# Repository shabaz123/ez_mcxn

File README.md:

# EZ-MCXN

This repository contains NXP MCXN related content.

# MCXN236 Test Board

This test board is intended for trying out the MCXN236VKLT microcontroller (100-pin HLQFP 0.5 mm package). The 235 variant is also possible, and there's a good chance the MCXN547VKLT microcontroller will work too.

# MCX Projects

This folder contains a board config and example blinky application source code. The folders may be hard-coded in places; the mcx\_projects folder can be placed at `c:\dev\projects` to keep things seamless, otherwise you may need to edit files.

# Environment Variables

The following user vars (environment variables) will need to be created:

`ARMGCC_DIR = C:\DEV\arm_gnu_toolchains\15.2.rel1 `(this folder should contain bin, include, lib folders and so on)

`MCUXPRESSO_SDK_ROOT = C:\dev\projects\mcuxpresso-sdk\mcuxsdk`

# Double Blinky

## Overview

Double Blinky is a simple MCUXpresso SDK project that blinks two LEDs.

The example uses:

* LED1: P3_6
* LED2: P3_1

Both LEDs are active high.

The project also provides a simple starting point for creating new projects using the EZ-MCXN board configuration.

## Prerequisites

The following are required:

* MCUXpresso SDK installed under `C:\dev\projects\mcuxpresso-sdk`
* Arm GNU Toolchain
* CMake and Ninja
* Python
* MCUXpresso Config Tools
* NXP Secure Provisioning SDK (SPSDK), installed by typing: `py -m pip install spsdk`
* `west`

The project workspace is expected to be:

```text
C:\dev\projects\mcx_projects
```

For example:

```text
C:\dev\projects\mcx_projects\
├── _boards\
│   └── ez_mcxn\
└── double_blinky\
```

The `MCUXPRESSO_SDK_ROOT` environment variable must point to the MCUXpresso SDK:

```text
C:\dev\projects\mcuxpresso-sdk\mcuxsdk
```

## Building the Project

Open PowerShell in the project directory:

```powershell
cd C:\dev\projects\mcx_projects\double_blinky
```

One-time, you may need to enable permissions by typing:
```
Unblock-File .\build.ps1
```

For a clean build:

```powershell
.\build.ps1 clean
.\build.ps1 build debug
```

The build output is placed in:

```text
double_blinky\output
```

The main generated files are:

```text
output\double_blinky.elf
output\double_blinky.bin
```

Useful build commands are:

```powershell
.\build.ps1
.\build.ps1 clean
.\build.ps1 debug
.\build.ps1 release
.\build.ps1 menuconfig
.\build.ps1 list
.\build.ps1 flash
```

The commands have the following purposes:

* `.\build.ps1` - Builds the project using the debug build configuration.
* `.\build.ps1 clean` - Cleans compiled files from the existing build. Use this after changing board files, Kconfig settings or CMake files, or if a normal build behaves unexpectedly. Also, do this whenever changing between debug and release builds.
* `.\build.ps1 release` - Builds the project using the debug build configuration.
* `.\build.ps1 menuconfig` - Opens the interactive Kconfig configuration interface, allowing SDK and project configuration options to be viewed or changed.
* `.\build.ps1 list` - Displays the project/build configuration being used by the script, such as the board, SDK, toolchain and build directory.
* * `.\build.ps1 flash` - Uses SPSDK to flash the microcontroller. Before executing this command, hold down the BOOT button and reset the microcontroller, then release the BOOT button.

For normal source-code changes, for debug builds, `.\build.ps1` is usually sufficient. Use `clean` after changing the board configuration, Kconfig files or CMake files.

## Creating a New Project

`double_blinky` can be used as a template for another application.

Copy the project folder and give it a new name. For example:

```text
C:\dev\projects\mcx_projects\testproj
```

Then:

1. In `CMakeLists.txt`, change the project name from `double_blinky` to `testproj`.
2. In `Kconfig`, change the displayed project name.
3. Modify `main.c` for the new application.
4. For VS Code IntelliSense Syntax Highlighting to work well, edit the file `mcx_projects\.vscode\c_cpp_properties.json` to add your project folder in the `compileCommands` section. Note: For IntelliSense to fully work, open the top folder `mcx_projects`, not the individual project folder. You may need to restart VS Code after performing a first build for each project, for IntelliSense to fully work, because it relies on a file that gets generated and placed in the project folder output subdirectory.
5. Build with:

```powershell
.\build.ps1 debug
```

The existing `ez_mcxn` board configuration can be shared by multiple projects.

## Board Configuration

Board configurations are stored in:

```text
C:\dev\projects\mcx_projects\_boards
```

The board used by this project is:

```text
C:\dev\projects\mcx_projects\_boards\ez_mcxn
```

The important files include:

```text
ez_mcxn\
├── board\
├── board.c
├── board.h
├── CMakeLists.txt
├── EZ_MXCN.mex
├── Kconfig
├── Kconfig.defconfig
├── prj.conf
└── variable.cmake
```

The `board` subfolder contains files generated by MCUXpresso Config Tools, such as:

```text
clock_config.c
clock_config.h
peripherals.c
peripherals.h
pin_mux.c
pin_mux.h
```

Do not normally edit these generated files manually.

## Adding or Modifying Peripherals

Launch MCUXpresso Config Tools and open:

```text
C:\dev\projects\mcx_projects\_boards\ez_mcxn\EZ_MXCN.mex
```

Use Config Tools to modify pins, clocks and peripherals.

When finished, use **Update Code** to regenerate the files in the `board` subfolder.

Then rebuild the application:

```powershell
.\build.ps1 clean
.\build.ps1 debug
```

## Creating a New Board Configuration

If a project needs different hardware without changing the shared `ez_mcxn` configuration, make a copy of the board folder.

For example:

```text
C:\dev\projects\mcx_projects\_boards\myboard
```

Update the board name where required, particularly in:

```text
Kconfig
variable.cmake
board.h
```

Rename the `.mex` file if desired, open it with MCUXpresso Config Tools, make the required pin, clock and peripheral changes, and run **Update Code**.

Finally, change the `$Board` setting in the project's `build.ps1`:

```powershell
$Board = "myboard"
```

Then perform a clean build.

## EZ-MCXN Hardware

The current EZ-MCXN configuration uses:

* MCU: MCXN236
* Main crystal: 24 MHz
* RTC crystal: 32.768 kHz
* System clock: 150 MHz
* LED1: P3_6, active high
* LED2: P3_1, active high
* UART RX: P1_8
* UART TX: P1_9
* UART: LP_FLEXCOMM4 / LPUART
* UART baud rate: 115200

## Debugging and Programming

### Using a Debug Probe

A compatible SWD debug probe, for example MCU-Link, can be used for programming and debugging.

Build the project first using:

```powershell
.\build.ps1 debug
```

The ELF file for debugging/programming is then available at:

```text
output\double_blinky.elf
```

### Programming Without a Debug Probe

The MCXN236 contains a ROM-based ISP (In-System Programming) bootloader. This makes it possible to program the internal flash without an SWD debug probe.

The ROM bootloader supports several communication interfaces, including USB HID.

The EZ-MCXN board has a USB connector connected to the MCU USB signals and push-buttons labelled `BOOT LOAD` and `RESET`.

To enter ROM ISP mode:

1. Connect the EZ-MCXN USB connector to the PC.
2. Press and hold `BOOT LOAD`.
3. While continuing to hold `BOOT LOAD`, press and release `RESET`.
4. Release `BOOT LOAD`.

The MCXN236 should now be running its built-in ROM ISP bootloader rather than the application in flash.

If you installed NXP SPSDK (mentioned earlier) then afer you've pressed the buttons to get into the bootloader mode, type:
```
.\build.ps1 flash
```

If all goes well, the new firmware will start running!

The PC can communicate with the ROM bootloader using NXP's `blhost` command-line utility or MCUXpresso Secure Provisioning Tool (the above command uses the Python SPSDK install, view the contents of the `build.ps1` file to see the commands that were used).

A useful first test with `blhost` is to ask the bootloader for its version/property information. For USB HID, `blhost` uses the USB VID/PID of the ROM bootloader.

For example, the MCXN236 ROM ISP used on NXP's FRDM-MCXN236 is accessible with:

```powershell
blhost -u 0x1FC9,0x0158 -- get-property 1
```

If this succeeds, the PC is communicating with the MCXN236 ROM bootloader.

The application binary produced by this project is:

```text
output\double_blinky.bin
```

For an unsecured development device using the normal internal-flash boot configuration, firmware can be written to the beginning of internal flash using the ROM ISP tools.

NXP's MCUXpresso Secure Provisioning Tool is recommended when initially setting up or verifying this process because it provides a GUI for selecting the MCXN236, establishing the ISP connection, preparing the image and programming the device.

After programming is complete, press `RESET` without holding `BOOT LOAD`. The MCU should then boot the application normally from internal flash.

> **Note:** ROM ISP is different from installing a custom USB DFU bootloader. The MCXN236 ROM bootloader is already built into the chip and cannot be accidentally erased with the application. Secure-boot, lifecycle and CMPA configuration can change what the ROM permits, so the simple procedure above assumes an unsecured development device with the normal internal-flash boot configuration.

# EZ_MCXN Pin Allocations
<!-- info: table: widths="6% 16% 6% 18% 6% 21% 6% 21%" -->

| Pin | Use           | Pin | Use               | Pin | Use       | Pin | Use                         |
| :-- | :------------ | :-- | :---------------- | :-- | :-------- | :-- | :-------------------------- |
| 1   | UART\_RXD     | 26  | HDR\_PORT4        | 51  | SPARE(TP) | 76  | SWDIO                       |
| 2   | UART\_TXD     | 27  | HDR\_PORT4        | 52  | 0V        | 77  | SWCLK                       |
| 3   | CANTX         | 28  | HDR\_PORT4        | 53  | N/C       | 78  | SWO                         |
| 4   | CANRX         | 29  | HDR\_PORT4        | 54  | 3.3V      | 79  | SPARE(TP)                   |
| 5   | HDR\_PORT1    | 30  | 3.3V via FBEAD    | 55  | Cap to 0V | 80  | PDM\_CLM                    |
| 6   | HDR\_PORT1    | 31  | 3.3V via FBEAD    | 56  | TFT\_DC   | 81  | PDM\_DAT                    |
| 7   | HDR\_PORT1    | 32  | 0V                | 57  | TFT\_RST  | 82  | BOOT\_BTN\_CAP\_AND\_PULLUP |
| 8   | HDR\_PORT1    | 33  | 0V                | 58  | Cap to 0V | 83  | 3.3V                        |
| 9   | RST (R/C/BTN) | 34  | 3.3V              | 59  | 3.3V      | 84  | I2C\_SDA                    |
| 10  | XTAL          | 35  | HDR\_PORT4GENERAL | 60  | TFT\_CS   | 85  | I2C\_SCL                    |
| 11  | EXTAL         | 36  | HDR\_PORT4GENERAL | 61  | TFT\_BL   | 86  | PDM\_DAT1                   |
| 12  | Short to 58   | 37  | HDR\_PORT4GENERAL | 62  | KEY\_ROW1 | 87  | SPARE(TP)                   |
| 13  | 3.3V          | 38  | HDR\_PORT4GENERAL | 63  | KEY\_ROW2 | 88  | microSD MOSI                |
| 14  | I2S\_A\_BCLK  | 39  | HDR\_PORT4GENERAL | 64  | KEY\_ROW3 | 89  | microSD SCK                 |
| 15  | I2S\_A\_LRCLK | 40  | USBDP             | 65  | KEY\_ROW4 | 90  | microSD MISO                |
| 16  | I2S\_B\_DAT   | 41  | USBDM             | 66  | 3.3V      | 91  | microSD CS                  |
| 17  | I2S\_A\_DAT   | 42  | USB\_VBUS         | 67  | KEY\_COL1 | 92  | TFT\_MOSI                   |
| 18  | I2S\_A\_DAT1  | 43  | 0V                | 68  | KEY\_COL2 | 93  | TFT\_SCK                    |
| 19  | I2S\_B\_DAT1  | 44  | 3.3V              | 69  | KEY\_COL3 | 94  | TFT\_MISO                   |
| 20  | I2S\_B\_BCLK  | 45  | NC/DP             | 70  | KEY\_COL4 | 95  | HDR\_PORT1                  |
| 21  | I2S\_B\_LRCLK | 46  | NC/DM             | 71  | I2S\_MCLK | 96  | 3.3V                        |
| 22  | HDR\_PORT4    | 47  | 3.3V              | 72  | LED1      | 97  | HDR\_PORT1                  |
| 23  | HDR\_PORT4    | 48  | EXTAL32K          | 73  | 3.3V      | 98  | HDR\_PORT1                  |
| 24  | HDR\_PORT4    | 49  | XTAL32K           | 74  | LED2      | 99  | HDR\_PORT1                  |
| 25  | HDR\_PORT4    | 50  | N/C               | 75  | TFT\_CS2  | 100 | HDR\_PORT1                  |

# EZ-MCXN Parts List

Here is the parts list for the EZ-MCXN board:

| Reference          | Qty | Value          | Description                                                          |
| ------------------ | --- | -------------- | -------------------------------------------------------------------- |
| R10, R11           | 2   | 5.1k           | 0603 Resistor                                                        |
| R12, R13, R16, R17 | 4   | 10k            | 0603 Resistor                                                        |
| R14, R15           | 2   | 1k             | 0603 Resistor                                                        |
| R20                | 1   | 0R             | 0402 zero-ohm Resistor                                               |
| C1-C12, C16        | 13  | 100n           | 0402 Ceramic Capacitor X7R                                           |
| C13-C15, C24, C25  | 5   | 1u             | 0603 Ceramic Capacitor X7R                                           |
| C17                | 1   | 4.7u           | 0805 Ceramic Capacitor X7R                                           |
| C18                | 1   | 2.2u           | 0805 Ceramic Capacitor X7R                                           |
| C19                | 1   | 10u            | 0805 Ceramic Capacitor X5R 10V                                       |
| C21, C22           | 2   | 10u            | Case B Tantalum Capacitor 10V e.g. TPSB106K016R0800                  |
| C23                | 1   | 1n             | 0603 Ceramic Capacitor                                               |
| C26, C27           | 2   | 4.7p           | 0603 Ceramic Capacitor                                               |
| C29                | 1   | 1u             | 0805 Ceramic Capacitor                                               |
| D1, D2             | 2   | LED            | 0805 LED (0603 fits too) D1=RED, D2=BLUE                             |
| D3, D4             | 2   | MBR0540        | SOD-123 Schottky Diode                                               |
| FB1, FB2           | 2   | BLM21AG121SH1D | SMD Ferrite Bead 0805 120 ohm                                        |
| J1                 | 1   | USB4085        | USB Type C Receptacle Through-Hole                                   |
| J2-J11             | 1   | Header         | Dual Row 2.54mm Pin Header (total 2 x 42 way, cut to required sizes) |
| J12                | 1   | MicroSD_socket | Same Sky MSD-4-A and possibly Molex 5027740891                       |
| J13                | 1   | Keypad         | 4x4 or 4x3 keypad and 7- or 8-way header pin or socket if required   |
| J14                | 1   | Terminal Block | 2-way Screw Terminal Block 3.5 or 3.81mm pitch                       |
| SW1-SW3            | 3   | SKQGAFE010     | Tact button SMD 5x5mm body 3.7x6.2mm pitch                           |
| SW4, SW5           | 2   | TS-1101        | Tact button SMD 6x3.6mm                                              |
| U1                 | 1   | MCXN236VKLT    | NXP  MCXN236/235/547VKLT HLQFP100                                    |
| U2                 | 1   | MIC5209-3.3YS  | 3.3V LDO SOT-223                                                     |
| U3                 | 1   | SRV05-4        | ESD Diode Array                                                      |
| Y1                 | 1   | 830108212309   | Wurth 24MHz Crystal SMD 2016 4-pin 2.0x1.6mm                         |
| Y2                 | 1   | 830009678      | Wurth 32.768kHz Crystal SMD 2-pin 3.2x1.5mm                          |

# MINI-MCXN Board
The MINI-MCXN is a very cut-down board, with just 8 GPIO exposed via a flat-flex connector, and pads for attaching wires to PDM mics.

## MINI-MCXN Parts List

| Reference | Qty | Value             | Description                                           |
| --------- | --- | ----------------- | ----------------------------------------------------- |
| C1-C12    | 12  | 100n              | 0402 Capacitor                                        |
| C13-C15   | 3   | 1u                | 0603 Capacitor                                        |
| C17       | 1   | 4.7u              | 0805 Capacitor                                        |
| C18       | 1   | 2.2u              | 0805 Capacitor                                        |
| C19       | 1   | 10u               | 0805 Capacitor                                        |
| C21, C22  | 2   | 10u               | Case B Tantalum Capacitor 10V e.g. TPSB106K016R0800   |
| C23       | 1   | 1n                | 0603 Capacitor                                        |
| C26, C27  | 2   | 4.7p              | 0402 Capacitor                                        |
| C29       | 1   | 1u                | 0805 Capacitor                                        |
| D1        | 1   | LED               | 0603 LED RED                                          |
| FB1, FB2  | 2   | BLM21AG121SH1D    | SMD Ferrite Bead 0805 120 ohm                         |
| J1        | 1   | USB4085           | USB Type C Receptacle Through-Hole                    |
| J2        | 1   | JST SH 4-way Conn | Connector JST SH SM04B-SRSS-TB 1mm pitch Horiz        |
| J5        | 1   | FFC_0.5MM 16-way  | FFC Connector Hirose FH12-16S-0.5SH 0.5mm pitch Horiz |
| R10, R11  | 2   | 5.1k              | 0402 Resistor                                         |
| R12, R13  | 2   | 10k               | 0402 Resistor                                         |
| R14       | 1   | 1k                | 0402 Resistor                                         |
| SW1-SW3   | 3   | SKQGAFE010        | Tact button SMD 5x5mm body 3.7x6.2mm pitch            |
| SW4, SW5  | 2   | Tact 4x3mm        | Tact button 4x3mm body 2-pin                          |
| U1        | 1   | MCXN236VKLT       | NXP MCXN236/235/547VKLT HLQFP100                      |
| U2        | 1   | MIC5209-3.3YS     | 3.3V LDO SOT-223                                      |
| U3        | 1   | SRV05-4           | ESD Diode Array                                       |
| Y1        | 1   | 830108212309      | Wurth 24MHz Crystal SMD 2016 4-pin 2.0x1.6mm          |

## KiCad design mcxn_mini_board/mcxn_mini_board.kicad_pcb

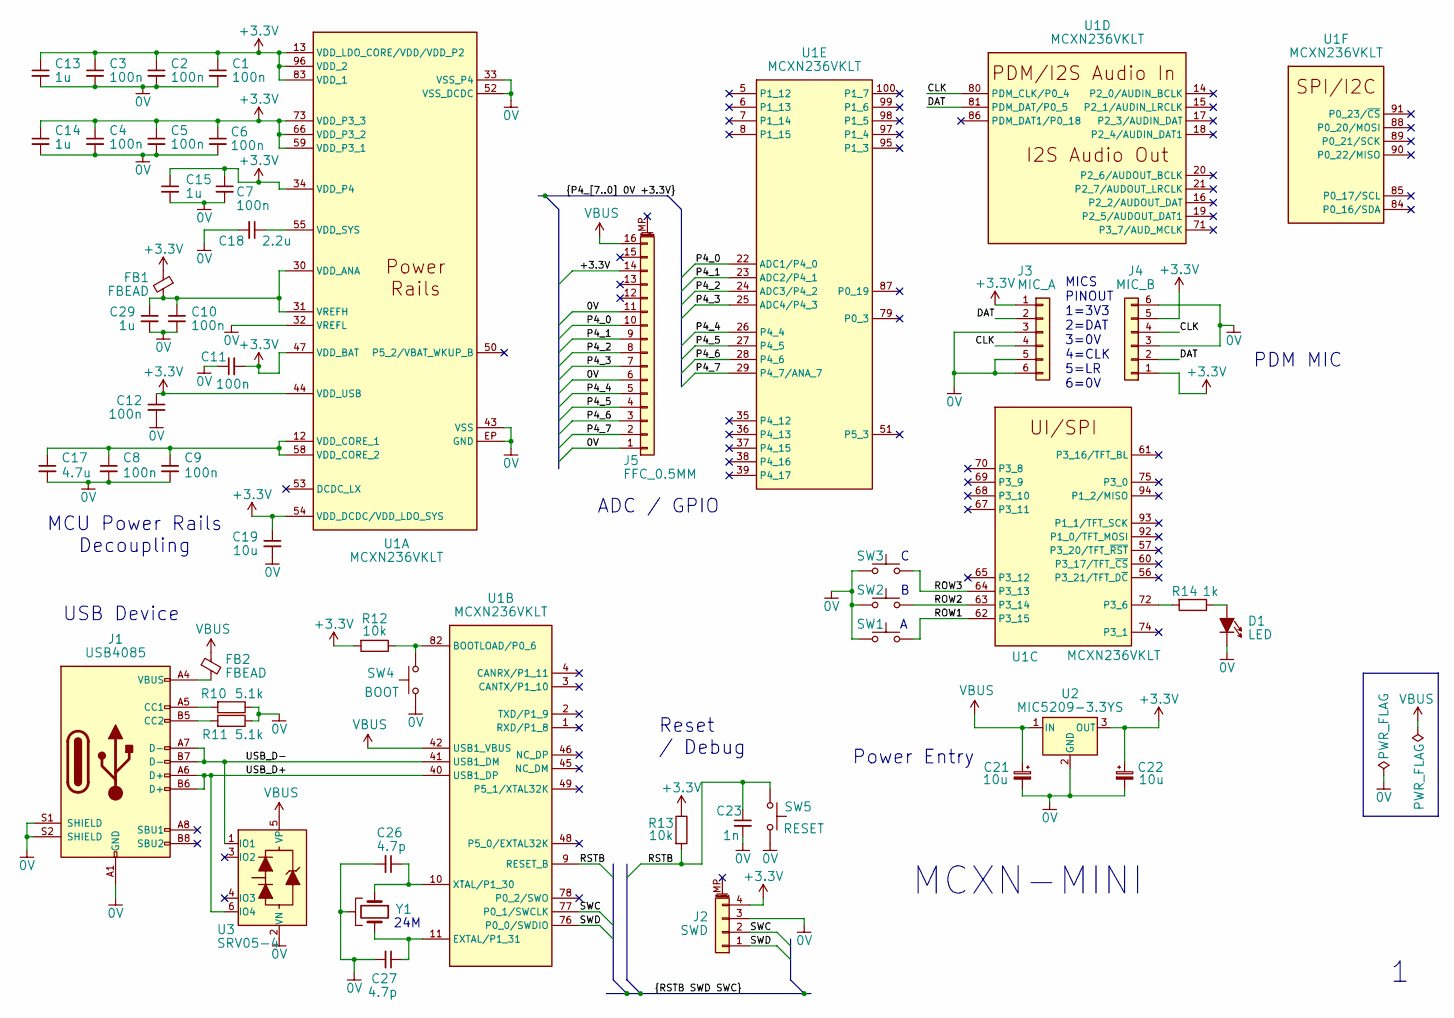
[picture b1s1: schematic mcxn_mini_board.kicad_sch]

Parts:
C1, C2, C3, C4, C5, C6, C7, C8, C9, C10, C11, C12: 100n; 0402-footprint-improved-Cap3D
C13, C14, C15: 1u; 0603-footprint-improved-Cap3D
C17: 4.7u; C_0805_2012Metric
C18: 2.2u; C_0805_2012Metric
C19: 10u; C_0805_2012Metric
C21, C22: 10u; Cap-Tant-CaseB
C23: 1n; 0603-footprint-improved-Cap3D
C26, C27: 4.7p; 0402-footprint-improved-Cap3D
C29: 1u; C_0805_2012Metric
D1: LED; LED_0603
FB1, FB2: FBEAD; BLM21AG121SH1D
J1: USB4085; USB_C_Receptacle_GCT_USB4085_improved; LCSC Part # C36936564
J2: SWD; JST_SH_SM04B-SRSS-TB_1x04-1MP_P1.00mm_Horizontal
J3: MIC_A; Pad_for_flex_1x06_P1.27mm
J4: MIC_B; Pad_for_flex_1x06_P1.27mm
J5: FFC_0.5MM; Hirose_FH12-16S-0.5SH_1x16-1MP_P0.50mm_Horizontal
R10, R11: 5.1k; 0402-footprint-improved-Res3D; LCSC Part # C723526
R12, R13: 10k; 0402-footprint-improved-Res3D; LCSC Part # C723526
R14: 1k; 0402-footprint-improved-Res3D; LCSC Part # C723526
SW1, SW2, SW3: SKQGAFE010; Tact-SW-TS-1101-6mm-3.6mm
SW4: BOOT; Tact-SW-4x3mm-body
SW5: RESET; Tact-SW-4x3mm-body
U1: MCXN236VKLT; HLQFP100-NXP; Manufacturer_Part_Number MCXN236VKLT; Mouser Part Number 771-MCXN236VKLT
U2: MIC5209-3.3YS; SOT-223
U3: SRV05-4
Y1: 830108212309; Crystal_SMD_2016-4Pin_2.0x1.6mm

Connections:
0V: C1.2, C2.2, C3.2, C4.2, C5.2, C6.2, C7.2, C8.2, C9.2, C10.2, C11.1, C12.2, C13.2, C14.2, C15.2, C17.2, C18.2, C19.2, C21.2, C22.2, C23.2, C26.2, C27.2, C29.2, D1.1 (K), J1.A1 (GND), J1.A12 (GND), J1.B1 (GND), J1.B12 (GND), J1.S1 (SHIELD), J1.S2 (SHIELD), J2.3, J3.3, J3.5, J3.6, J4.3, J4.6, J5.1, J5.6, J5.11, R10.1, R11.1, SW1.1, SW2.1, SW3.1, SW4.1, SW5.1, U1.32 (VREFL), U1.33 (VSS_P4), U1.43 (VSS), U1.52 (VSS_DCDC), U1.EP (GND), U2.2 (GND), U3.2 (VN), Y1.2, Y1.4 (2)
+3.3V: C1.1, C2.1, C3.1, C4.1, C5.1, C6.1, C7.1, C11.2, C12.1, C13.1, C14.1, C15.1, C19.1, C22.1, FB1.1, J2.4, J3.1, J4.1, J4.5, J5.14, R12.2, R13.1, U1.13 (VDD_LDO_CORE/VDD/VDD_P2), U1.34 (VDD_P4), U1.44 (VDD_USB), U1.47 (VDD_BAT), U1.54 (VDD_DCDC/VDD_LDO_SYS), U1.59 (VDD_P3_1), U1.66 (VDD_P3_2), U1.73 (VDD_P3_3), U1.83 (VDD_1), U1.96 (VDD_2), U2.3 (OUT)
/CLK: J3.4, J4.4, U1.80 (PDM_CLK/P0_4)
/DAT: J3.2, J4.2, U1.81 (PDM_DAT/P0_5)
/P4_0: J5.10, U1.22 (ADC1/P4_0)
/P4_1: J5.9, U1.23 (ADC2/P4_1)
/P4_2: J5.8, U1.24 (ADC3/P4_2)
/P4_3: J5.7, U1.25 (ADC4/P4_3)
/P4_4: J5.5, U1.26 (P4_4)
/P4_5: J5.4, U1.27 (P4_5)
/P4_6: J5.3, U1.28 (P4_6)
/P4_7: J5.2, U1.29 (P4_7/ANA_7)
/ROW1: SW1.2, U1.62 (P3_15)
/ROW2: SW2.2, U1.63 (P3_14)
/ROW3: SW3.2, U1.64 (P3_13)
/RSTB: C23.1, R13.2, SW5.2, U1.9 (RESET_B)
/SWC: J2.2, U1.77 (P0_1/SWCLK)
/SWD: J2.1, U1.76 (P0_0/SWDIO)
/USB_D+: J1.A6 (D+), J1.B6 (D+), U1.40 (USB1_DP), U3.6 (IO4)
/USB_D-: J1.A7 (D-), J1.B7 (D-), U1.41 (USB1_DM), U3.1 (IO1)
unnamed: D1.2 (A), R14.1
unnamed: FB2.2, J1.A4 (VBUS), J1.A9 (VBUS), J1.B4 (VBUS), J1.B9 (VBUS)
unnamed: J1.A5 (CC1), R10.2
unnamed: J1.B5 (CC2), R11.2
unnamed: C10.1, C29.1, FB1.2, U1.30 (VDD_ANA), U1.31 (VREFH)
unnamed: C8.1, C9.1, C17.1, U1.12 (VDD_CORE_1), U1.58 (VDD_CORE_2)
unnamed: C18.1, U1.55 (VDD_SYS)
unnamed: R14.2, U1.72 (P3_6)
unnamed: R12.1, SW4.2, U1.82 (BOOTLOAD/P0_6)
unnamed: C27.1, U1.11 (EXTAL/P1_31), Y1.3
unnamed: C26.1, U1.10 (XTAL/P1_30), Y1.1
VBUS: C21.1, FB2.1, J5.16, U1.42 (USB1_VBUS), U2.1 (IN), U3.5 (VP)

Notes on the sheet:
Reset / Debug
MCU Power Rails Decoupling
24M
MCXN-MINI
ADC / GPIO
MICS PINOUT 1=3V3 2=DAT 3=0V 4=CLK 5=LR 6=0V
PDM MIC
USB Device
Power Entry

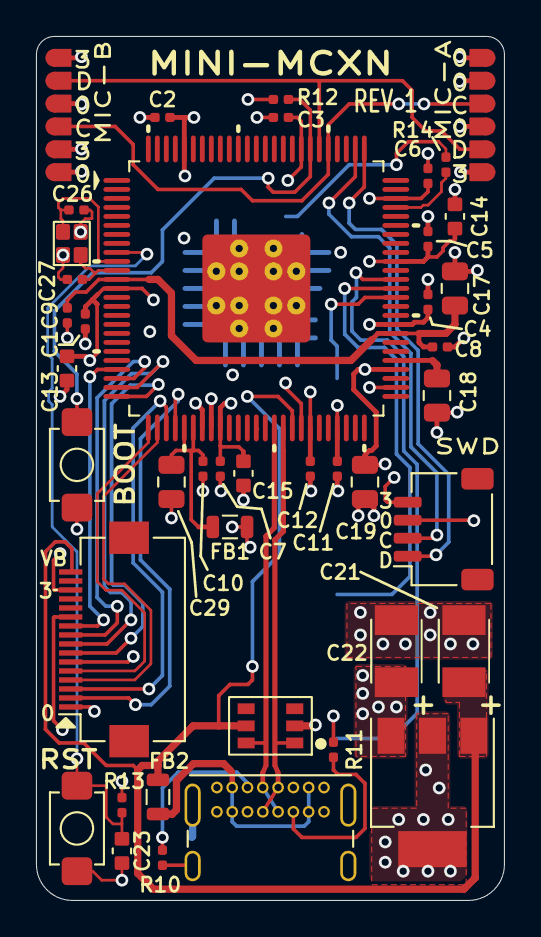
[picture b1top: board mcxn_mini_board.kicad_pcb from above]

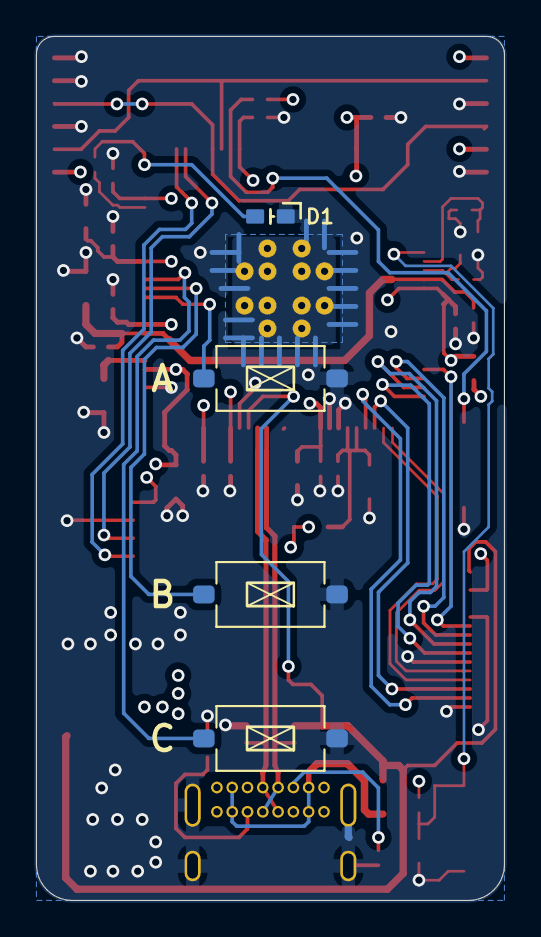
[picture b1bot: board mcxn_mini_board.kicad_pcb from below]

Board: 4 copper layers, 26.0 x 48.0 mm, 46 parts (4 on the bottom side), 32 nets.

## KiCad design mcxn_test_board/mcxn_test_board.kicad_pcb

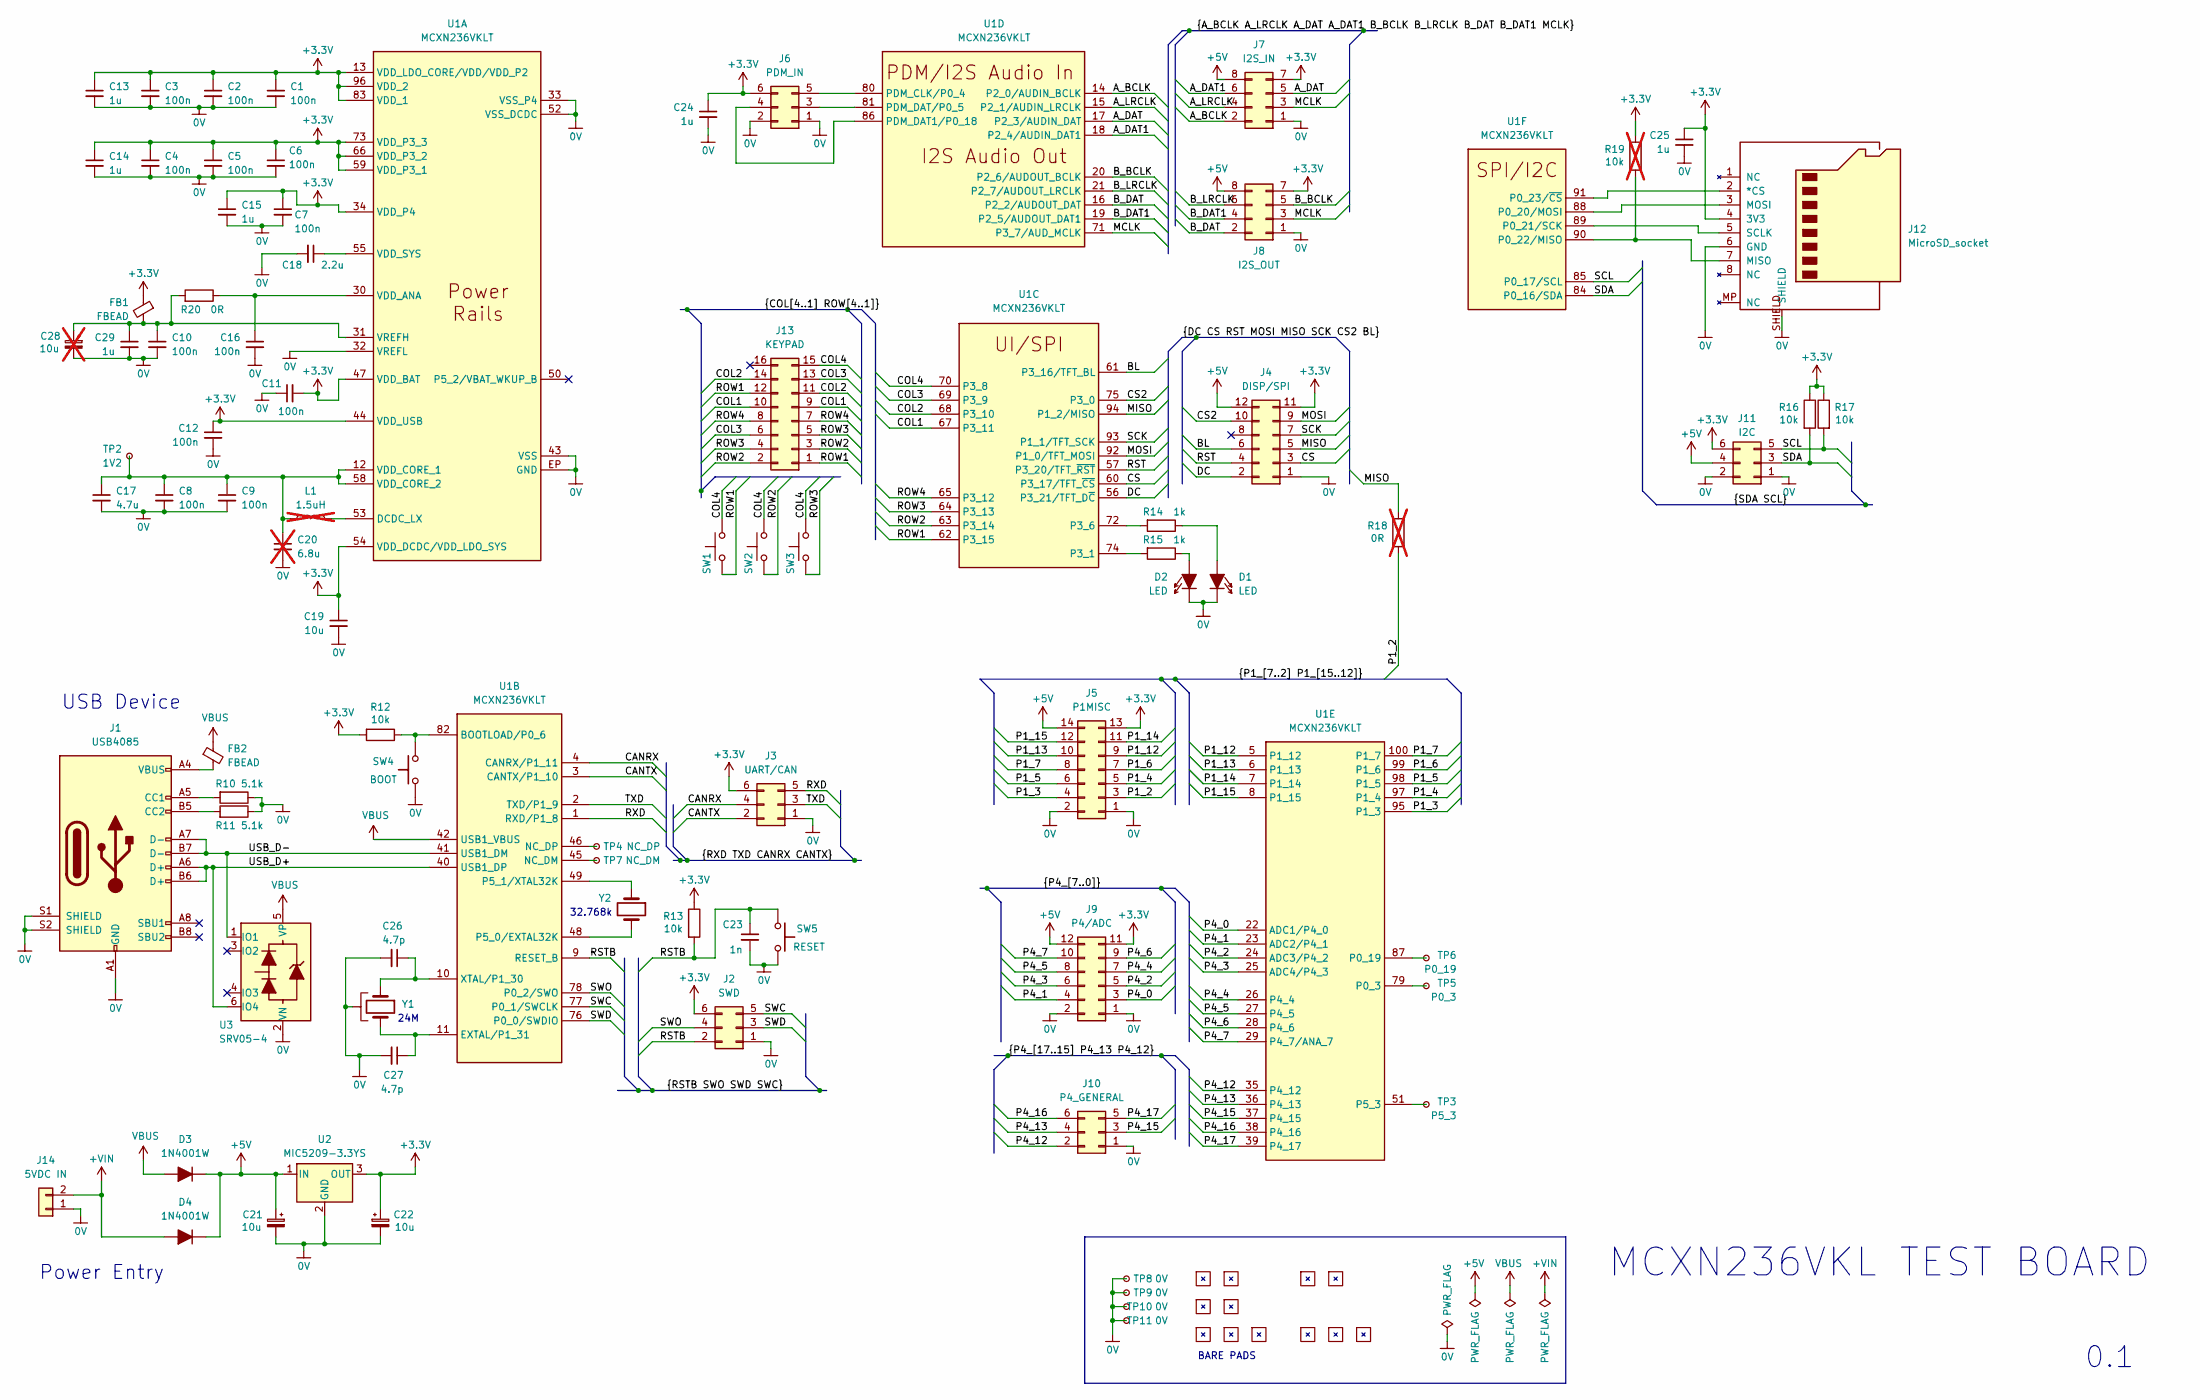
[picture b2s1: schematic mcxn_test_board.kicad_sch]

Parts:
C1, C2, C3, C4, C5, C6, C7, C8, C9, C10, C11, C12, C16: 100n; 0402-footprint-improved-Cap3D
C13, C14, C15, C24, C25: 1u; 0603-footprint-improved-Cap3D
C17: 4.7u; C_0805_2012Metric
C18: 2.2u; C_0805_2012Metric
C19: 10u; C_0805_2012Metric
C20: 6.8u; C_0805_2012Metric; not fitted
C21, C22: 10u; Cap-Tant-CaseB
C23: 1n; 0603-footprint-improved-Cap3D
C26, C27: 4.7p; 0603-footprint-improved-Cap3D
C28: 10u; Cap-Tant-CaseB; not fitted
C29: 1u; C_0805_2012Metric
D1, D2: LED; LED_0603_or_0805
D3, D4: 1N4001W; D_SOD-123-pins12
FB1, FB2: FBEAD; BLM21AG121SH1D
J1: USB4085; USB_C_Receptacle_GCT_USB4085_improved; LCSC Part # C36936564
J2: SWD; PinHeader_2x03_P2.54mm_Vertical
J3: UART/CAN; PinHeader_2x03_P2.54mm_Vertical
J4: DISP/SPI; PinHeader_2x06_P2.54mm_Vertical
J5: P1MISC; PinHeader_2x07_P2.54mm_Vertical
J6: PDM_IN; PinHeader_2x03_P2.54mm_Vertical
J7: I2S_IN; PinHeader_2x04_P2.54mm_Vertical
J8: I2S_OUT; PinHeader_2x04_P2.54mm_Vertical
J9: P4/ADC; PinHeader_2x06_P2.54mm_Vertical
J10: P4_GENERAL; PinHeader_2x03_P2.54mm_Vertical
J11: I2C; PinHeader_2x03_P2.54mm_Vertical
J12: MicroSD_socket; microsd-generic
J13: KEYPAD; PinHeader_2x08_P2.54mm_Vertical
J14: 5VDC IN; TerminalBlock_2way-3.5-3.81mm
L1: 1.5uH; L_Bourns-SRN2510; not fitted
R10, R11: 5.1k; 0603-footprint-improved-Res3D; LCSC Part # C723526
R12, R13, R16, R17: 10k; 0603-footprint-improved-Res3D; LCSC Part # C723526
R14, R15: 1k; 0603-footprint-improved-Res3D; LCSC Part # C723526
R18: 0R; 0603-footprint-improved-Res3D; LCSC Part # C723526; not fitted
R19: 10k; 0603-footprint-improved-Res3D; LCSC Part # C723526; not fitted
R20: 0R; 0402-footprint-improved-Res3D; LCSC Part # C723526
SW1, SW2, SW3: SKQGAFE010
SW4: BOOT; Tact-SW-TS-1101-6mm-3.6mm; LCSC Part # C500065
SW5: RESET; Tact-SW-TS-1101-6mm-3.6mm; LCSC Part # C500065
TP2: 1V2; TestPoint_Pad_D1.0mm
TP3: P5_3; TestPoint_Pad_D1.0mm
TP4: NC_DP; TestPoint_Pad_D1.0mm
TP5: P0_3; TestPoint_Pad_D1.0mm
TP6: P0_19; TestPoint_Pad_D1.0mm
TP7: NC_DM; TestPoint_Pad_D1.0mm
TP8, TP9, TP10, TP11: 0V; TestPoint_Plated_Hole_0.6mm
U1: MCXN236VKLT; HLQFP100-NXP; Manufacturer_Part_Number MCXN236VKLT; Mouser Part Number 771-MCXN236VKLT
U2: MIC5209-3.3YS; SOT-223
U3: SRV05-4
U4, U5, U9, U13, U16, U17: bare-pad-3x3
U6, U7: bare-pad-2x2
U8, U10, U11, U14: bare-pad-2x1
Y1: 830108212309; Crystal_SMD_2016-4Pin_2.0x1.6mm
Y2: 830009678; Crystal_SMD-2Pin_3.2x1.5mm

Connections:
0V: C1.2, C2.2, C3.2, C4.2, C5.2, C6.2, C7.2, C8.2, C9.2, C10.2, C11.1, C12.2, C13.2, C14.2, C15.2, C16.2, C17.2, C18.2, C19.2, C20.2, C21.2, C22.2, C23.2, C24.2, C25.2, C26.2, C27.2, C28.2, C29.2, D1.1 (K), D2.1 (K), J1.A1 (GND), J1.A12 (GND), J1.B1 (GND), J1.B12 (GND), J1.S1 (SHIELD), J1.S2 (SHIELD), J2.1, J3.1, J4.1, J5.1, J5.2, J6.1, J6.2, J7.1, J8.1, J9.1, J9.2, J10.1, J11.1, J11.2, J12.6 (GND), J12.SHIELD, J14.1, R10.1, R11.1, SW4.1, SW5.1, TP8.1 (1_1), TP9.1 (1_1), TP10.1 (1_1), TP11.1 (1_1), U1.32 (VREFL), U1.33 (VSS_P4), U1.43 (VSS), U1.52 (VSS_DCDC), U1.EP (GND), U2.2 (GND), U3.2 (VN), Y1.2, Y1.4 (2)
+3.3V: C1.1, C2.1, C3.1, C4.1, C5.1, C6.1, C7.1, C11.2, C12.1, C13.1, C14.1, C15.1, C19.1, C22.1, C24.1, C25.1, FB1.1, J2.6, J3.6, J4.11, J5.13, J6.6, J7.7, J8.7, J9.11, J11.6, J12.4 (3V3), R12.2, R13.1, R16.1, R17.1, R19.1, U1.13 (VDD_LDO_CORE/VDD/VDD_P2), U1.34 (VDD_P4), U1.44 (VDD_USB), U1.47 (VDD_BAT), U1.54 (VDD_DCDC/VDD_LDO_SYS), U1.59 (VDD_P3_1), U1.66 (VDD_P3_2), U1.73 (VDD_P3_3), U1.83 (VDD_1), U1.96 (VDD_2), U2.3 (OUT)
+5V: C21.1, D3.1 (K), D4.1 (K), J4.12, J5.14, J7.8, J8.8, J9.12, J11.4, U2.1 (IN)
+VIN: D4.2 (A), J14.2
/A_BCLK: J7.2, U1.14 (P2_0/AUDIN_BCLK)
/A_DAT: J7.5, U1.17 (P2_3/AUDIN_DAT)
/A_DAT1: J7.6, U1.18 (P2_4/AUDIN_DAT1)
/A_LRCLK: J7.4, U1.15 (P2_1/AUDIN_LRCLK)
/BL: J4.6, U1.61 (P3_16/TFT_BL)
/B_BCLK: J8.5, U1.20 (P2_6/AUDOUT_BCLK)
/B_DAT: J8.2, U1.16 (P2_2/AUDOUT_DAT)
/B_DAT1: J8.4, U1.19 (P2_5/AUDOUT_DAT1)
/B_LRCLK: J8.6, U1.21 (P2_7/AUDOUT_LRCLK)
/CANRX: J3.4, U1.4 (CANRX/P1_11)
/CANTX: J3.2, U1.3 (CANTX/P1_10)
/COL1: J13.9, J13.10, U1.67 (P3_11)
/COL2: J13.11, J13.14, U1.68 (P3_10)
/COL3: J13.6, J13.13, U1.69 (P3_9)
/COL4: J13.15, SW1.2, SW2.2, SW3.2, U1.70 (P3_8)
/CS: J4.3, U1.60 (P3_17/TFT_~CS)
/CS2: J4.10, U1.75 (P3_0)
/DC: J4.2, U1.56 (P3_21/TFT_D~C)
/MCLK: J7.3, J8.3, U1.71 (P3_7/AUD_MCLK)
/MISO: J4.5, R18.1, U1.94 (P1_2/MISO)
/MOSI: J4.9, U1.92 (P1_0/TFT_MOSI)
/P1_2: J5.3, R18.2
/P1_3: J5.4, U1.95 (P1_3)
/P1_4: J5.5, U1.97 (P1_4)
/P1_5: J5.6, U1.98 (P1_5)
/P1_6: J5.7, U1.99 (P1_6)
/P1_7: J5.8, U1.100 (P1_7)
/P1_12: J5.9, U1.5 (P1_12)
/P1_13: J5.10, U1.6 (P1_13)
/P1_14: J5.11, U1.7 (P1_14)
/P1_15: J5.12, U1.8 (P1_15)
/P4_0: J9.3, U1.22 (ADC1/P4_0)
/P4_1: J9.4, U1.23 (ADC2/P4_1)
/P4_2: J9.5, U1.24 (ADC3/P4_2)
/P4_3: J9.6, U1.25 (ADC4/P4_3)
/P4_4: J9.7, U1.26 (P4_4)
/P4_5: J9.8, U1.27 (P4_5)
/P4_6: J9.9, U1.28 (P4_6)
/P4_7: J9.10, U1.29 (P4_7/ANA_7)
/P4_12: J10.2, U1.35 (P4_12)
/P4_13: J10.4, U1.36 (P4_13)
/P4_15: J10.3, U1.37 (P4_15)
/P4_16: J10.6, U1.38 (P4_16)
/P4_17: J10.5, U1.39 (P4_17)
/ROW1: J13.1, J13.12, SW1.1, U1.62 (P3_15)
/ROW2: J13.2, J13.3, SW2.1, U1.63 (P3_14)
/ROW3: J13.4, J13.5, SW3.1, U1.64 (P3_13)
/ROW4: J13.7, J13.8, U1.65 (P3_12)
/RST: J4.4, U1.57 (P3_20/TFT_~RST)
/RSTB: C23.1, J2.2, R13.2, SW5.2, U1.9 (RESET_B)
/RXD: J3.5, U1.1 (RXD/P1_8)
/SCK: J4.7, U1.93 (P1_1/TFT_SCK)
/SCL: J11.5, R17.2, U1.85 (P0_17/SCL)
/SDA: J11.3, R16.2, U1.84 (P0_16/SDA)
/SWC: J2.5, U1.77 (P0_1/SWCLK)
/SWD: J2.3, U1.76 (P0_0/SWDIO)
/SWO: J2.4, U1.78 (P0_2/SWO)
/TXD: J3.3, U1.2 (TXD/P1_9)
/USB_D+: J1.A6 (D+), J1.B6 (D+), U1.40 (USB1_DP), U3.6 (IO4)
/USB_D-: J1.A7 (D-), J1.B7 (D-), U1.41 (USB1_DM), U3.1 (IO1)
unnamed: D1.2 (A), R14.1
unnamed: D2.2 (A), R15.1
unnamed: FB2.2, J1.A4 (VBUS), J1.A9 (VBUS), J1.B4 (VBUS), J1.B9 (VBUS)
unnamed: J1.A5 (CC1), R10.2
unnamed: J1.B5 (CC2), R11.2
unnamed: J6.3, U1.81 (PDM_DAT/P0_5)
unnamed: J6.4, U1.86 (PDM_DAT1/P0_18)
unnamed: J6.5, U1.80 (PDM_CLK/P0_4)
unnamed: J12.2 (*CS), U1.91 (P0_23/~CS)
unnamed: J12.7 (MISO), R19.2, U1.90 (P0_22/MISO)
unnamed: J12.3 (MOSI), U1.88 (P0_20/MOSI)
unnamed: J12.5 (SCLK), U1.89 (P0_21/SCK)
unnamed: L1.2, U1.53 (DCDC_LX)
unnamed: C16.1, R20.1, U1.30 (VDD_ANA)
unnamed: C8.1, C9.1, C17.1, C20.1, L1.1, TP2.1 (1_1), U1.12 (VDD_CORE_1), U1.58 (VDD_CORE_2)
unnamed: C18.1, U1.55 (VDD_SYS)
unnamed: C10.1, C28.1, C29.1, FB1.2, R20.2, U1.31 (VREFH)
unnamed: R15.2, U1.74 (P3_1)
unnamed: R14.2, U1.72 (P3_6)
unnamed: TP5.1 (1_1), U1.79 (P0_3)
unnamed: TP6.1 (1_1), U1.87 (P0_19)
unnamed: TP3.1 (1_1), U1.51 (P5_3)
unnamed: R12.1, SW4.2, U1.82 (BOOTLOAD/P0_6)
unnamed: C27.1, U1.11 (EXTAL/P1_31), Y1.3
unnamed: TP7.1 (1_1), U1.45 (NC_DM)
unnamed: TP4.1 (1_1), U1.46 (NC_DP)
unnamed: U1.48 (P5_0/EXTAL32K), Y2.2
unnamed: U1.49 (P5_1/XTAL32K), Y2.1
unnamed: C26.1, U1.10 (XTAL/P1_30), Y1.1
VBUS: D3.2 (A), FB2.1, U1.42 (USB1_VBUS), U3.5 (VP)

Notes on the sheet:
24M
MCXN236VKL TEST BOARD
BARE PADS
0.1
32.768k
USB Device
Power Entry

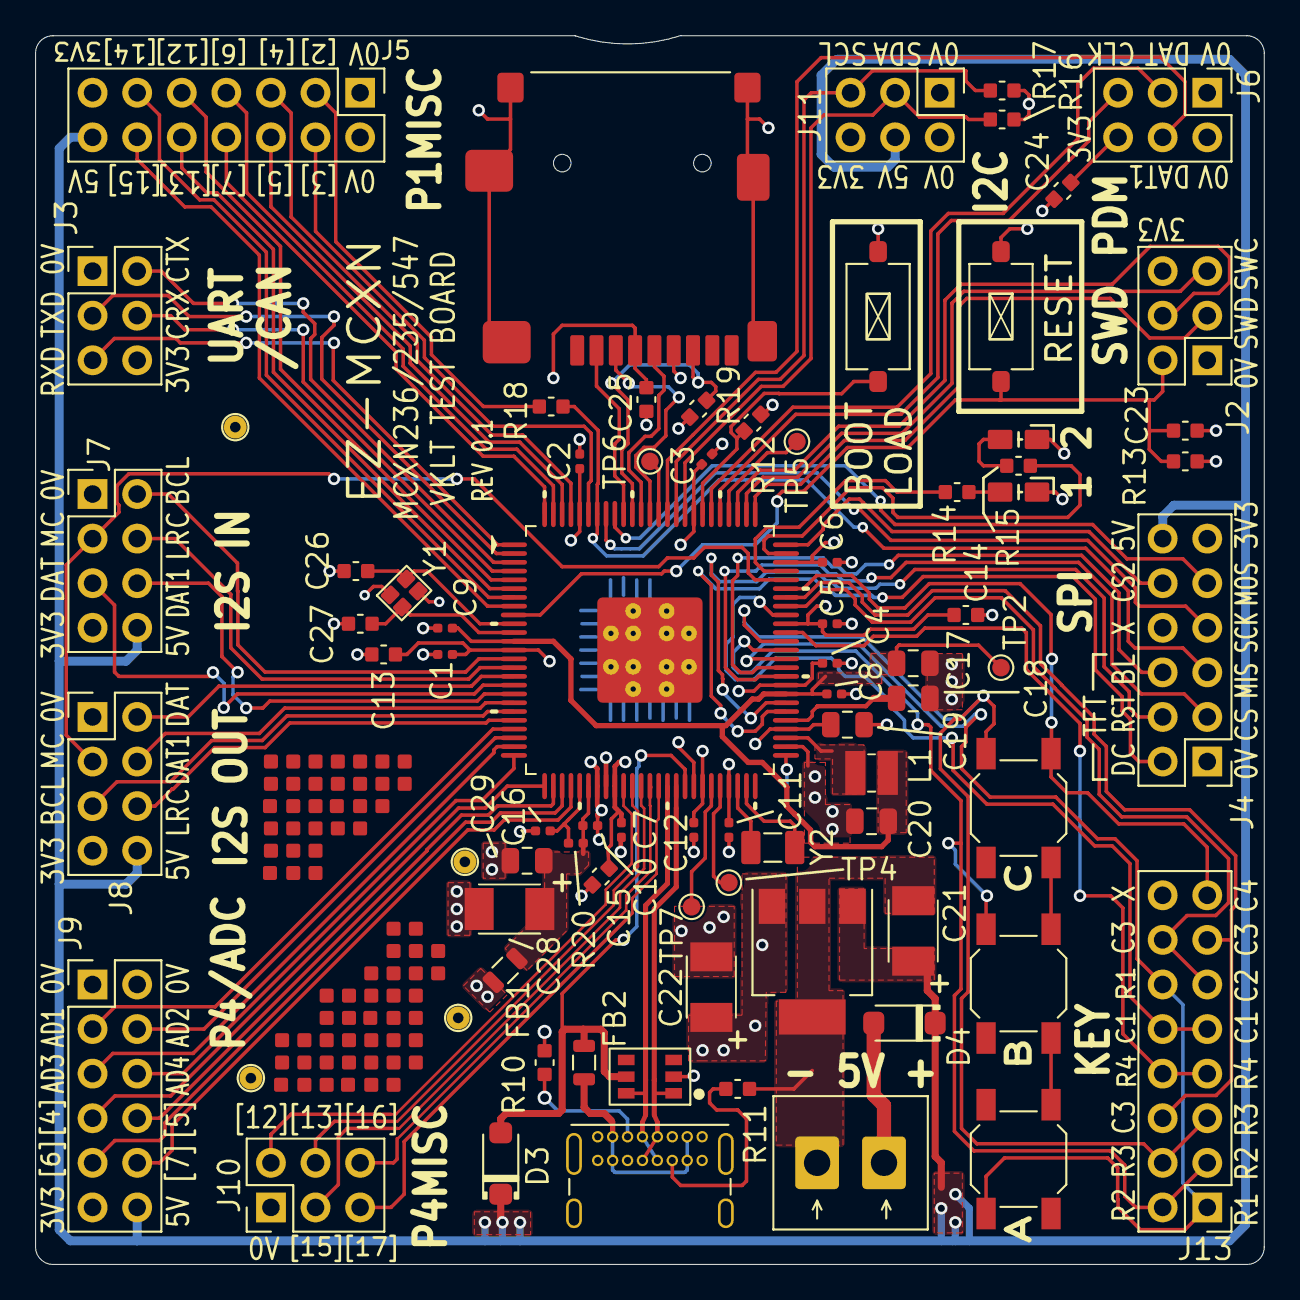
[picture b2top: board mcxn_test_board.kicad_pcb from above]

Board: 4 copper layers, 70.0 x 70.0 mm, 93 parts (1 on the bottom side), 94 nets.
